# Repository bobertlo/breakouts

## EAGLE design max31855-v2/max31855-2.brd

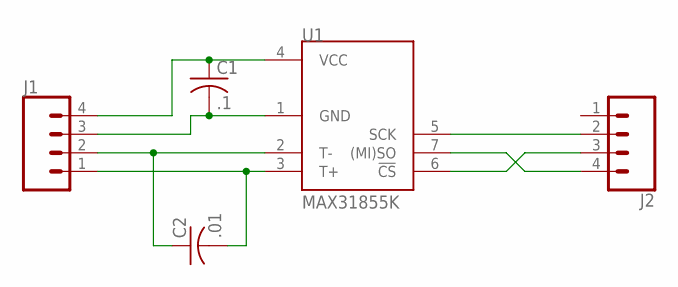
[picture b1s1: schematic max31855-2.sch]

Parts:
C1: .1; C0805
C2: .01; C0805
J1, J2: CONN_04; 1X04
U1: MAX31855K; SO08

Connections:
unnamed: J2.4, U1.7 ((MI)SO)
unnamed: J2.3, U1.6 (!CS)
unnamed: J2.2, U1.5 (SCK)
unnamed: C2.2, J1.1, U1.3 (T+)
unnamed: C2.1, J1.2, U1.2 (T-)
unnamed: C1.1, J1.4, U1.4 (VCC)
unnamed: C1.2, J1.3, U1.1 (GND)

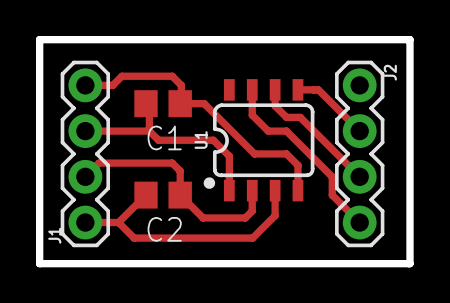
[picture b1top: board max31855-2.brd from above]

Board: 2 copper layers, 20.6 x 12.4 mm, 5 parts (0 on the bottom side), 7 nets.

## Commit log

2017-04-19 first commit. max31855
2017-04-20 max31855-v2 added
2017-04-20 fixed drill ex file and rebuilt gcode files to different specs

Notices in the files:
parts and their libraries:
SparkFun-IC-Conversion: Licensing: Creative Commons ShareAlike 4.0 International - https://creativecommons.org/licenses/by-sa/4.0
